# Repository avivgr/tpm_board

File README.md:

## A PCB for OPTIGA™ SLB 9670 TPM2.0

### Description

This is a KiCad project for a simple breakout PCB around the OPTIGA™ SLB 9670 TPM2.0 chip. The OPTIGA™ SLB 9670 TPM2.0 uses the SPI serial interface to a host. You can connect this board to a PC motherboard (using jumper wires), or to an SBC like the raspberry pi (more details below).

### Why?

Because there is a price hike on TPM2.0 boards due to Windows 11 requirements. Also, this is a great learning tool for TPM2.0 technology, instead of using a software emulated TPM.

### BOM

Reference(s) | Value
---|---
C1 | 1uF
C2 | 100nF
C3 | 100nF
IC1 | SLB9670VQ20FW785XUMA1
J1 | Conn_01x08_Female
R1 | 10k ohm

### Connecting to the raspberry pi

#### Wiring
Connect the board power pin to the 3.3v on the pi, also connect ground. Connect the SPI MISO, MOSI, and SCLK pins. The Chip Select (CS) pin should be connected to SPI_CE0 pin on the raspberry pi. You can leave the RST and PIRQ pins unconneced.

#### Update the device tree on the raspberry pi to detect the SLB 9670

Create a small tpm.dts file on the pi, with the following contents:

```
/*
* Device Tree overlay for Infineon SLx 9670
*/
/dts-v1/;
/plugin/;
/ {
	compatible = "brcm,bcm2835", "brcm,bcm2708", "brcm,bcm2709";
	fragment@0 {
		target = <&spi0>;
		__overlay__ {
			status = "okay";
		};
	};
	fragment@1 {
		target = <&spidev0>;
		__overlay__ {
			status = "disabled";
		};
	};
	fragment@2 {
		target = <&spi0>;
		__overlay__ {
			/* needed to avoid dtc warning */
			#address-cells = <1>;
			#size-cells = <0>;
			slb9670: slb9670@0{
				compatible = "infineon,slb9670";
				reg = <0>; /* CE0 */
				#address-cells = <1>;
				#size-cells = <0>;
				spi-max-frequency = <32000000>;
				status = "okay";
			};
		};
	};
};
```

compile the `tpm.dts` file into `tpm.dtbo` binary using the `dtc` tool (install using apt install as needed):   
```
$ dtc -@ -I dts -O dtb -o tpm.dtbo tpm.dts
```

Finally, copy the compiled overlay file to the overlay directory:
```
sudo cp tpm.dtbo /boot/overlays/
```

And reboot. You should see the following output in dmesg indicating success:
```
...
[   46.308765] tpm_tis_spi spi0.0: 2.0 TPM (device-id 0x1B, rev-id 22)
...
```
and the following device files are created:
```
$ ls -la /dev/tpm*

crw-rw---- 1 tss root  10,   224 Apr 26 16:44 /dev/tpm0
crw-rw---- 1 tss tss  239, 65536 Apr 26 16:44 /dev/tpmrm0
```

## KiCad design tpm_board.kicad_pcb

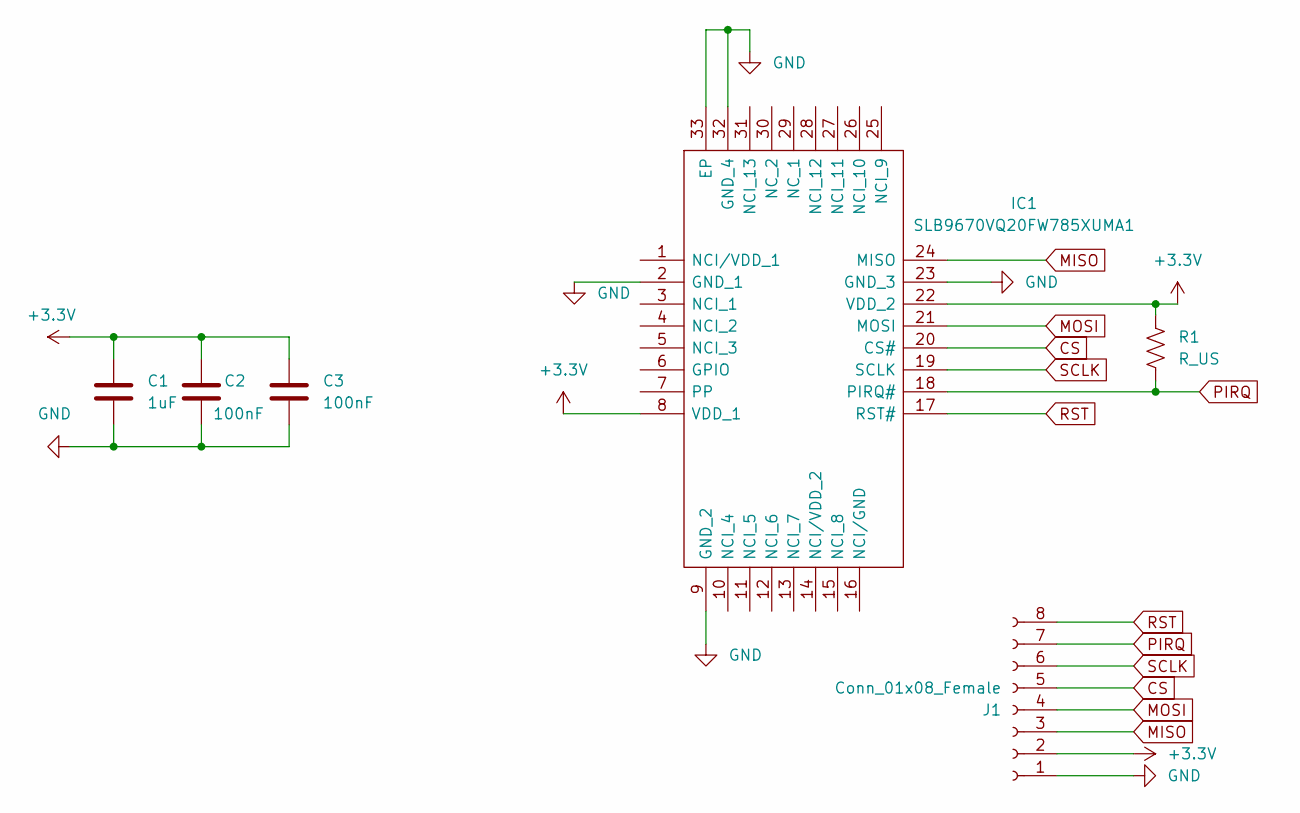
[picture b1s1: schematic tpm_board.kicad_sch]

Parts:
C1: 1uF; C_0805_2012Metric
C2, C3: 100nF; C_0805_2012Metric
IC1: SLB9670VQ20FW785XUMA1; Mouser Part Number 726-SLB9670VQ20FW785
J1: Conn_01x08_Female; PinHeader_1x08_P2.54mm_Vertical
R1: R_US; R_0805_2012Metric

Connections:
+3.3V: C1.1, C2.1, C3.1, IC1.8 (VDD_1), IC1.22 (VDD_2), J1.2, R1.1
CS: IC1.20 (CS#), J1.5
GND: C1.2, C2.2, C3.2, IC1.2 (GND_1), IC1.9 (GND_2), IC1.23 (GND_3), IC1.32 (GND_4), IC1.33 (EP), J1.1
MISO: IC1.24 (MISO), J1.3
MOSI: IC1.21 (MOSI), J1.4
PIRQ: IC1.18 (PIRQ#), J1.7, R1.2
RST: IC1.17 (RST#), J1.8
SCLK: IC1.19 (SCLK), J1.6

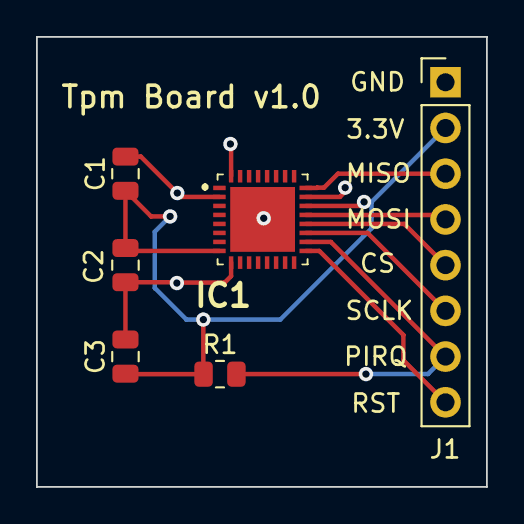
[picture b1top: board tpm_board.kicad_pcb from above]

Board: 2 copper layers, 25.0 x 25.0 mm, 6 parts (0 on the bottom side), 8 nets.

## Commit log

2022-09-06 Add 'README.md'
2022-09-06 add assets
2022-09-06 Update 'README.md'
    link to asset images
2022-09-06 Update 'README.md'
2023-07-19 Update README.md with BOM
